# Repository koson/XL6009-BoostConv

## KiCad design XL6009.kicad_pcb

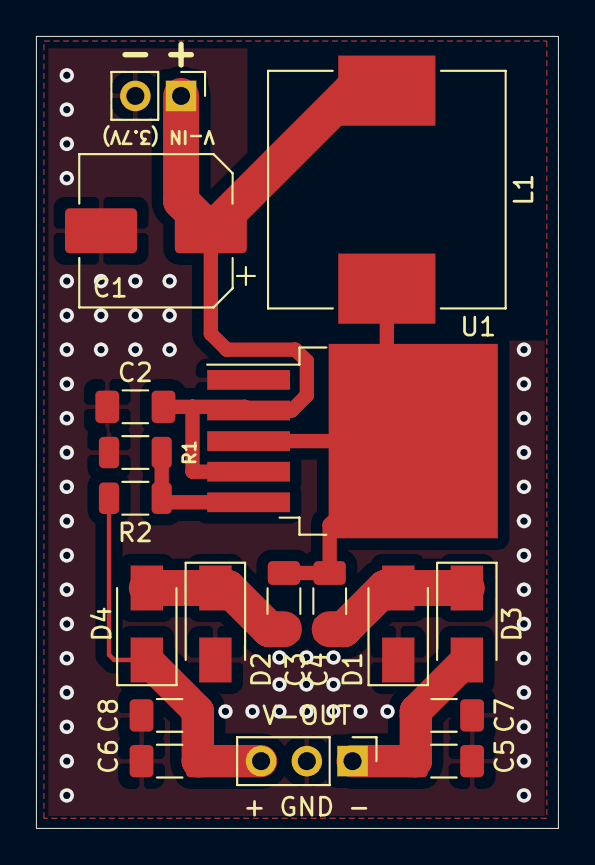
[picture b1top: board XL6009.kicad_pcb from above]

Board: 2 copper layers, 29.0 x 44.0 mm, 18 parts (0 on the bottom side), 8 nets.

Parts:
C1: 330u; CP_Elec_8x6.5
C2, C3, C4, C5, C6, C7, C8: 10u; C_1206_3216Metric_Pad1.33x1.80mm_HandSolder
D1, D2, D3, D4: SS34; D_SMA
J1: Conn_01x02_Female; PinHeader_1x02_P2.54mm_Vertical
J2: Conn_01x03_Female; PinHeader_1x03_P2.54mm_Vertical
L1: 22uH / 2A; L_Neosid_SM-NE127_HandSoldering
R1: RFB2; R_1206_3216Metric
R2: RFB1; R_1206_3216Metric
U1: XL6009; TO-263-5_TabPin3

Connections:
GND: C1.2, C2.1, C5.2, C6.1, C7.2, C8.1, D1.1, D2.2, J1.2, J2.2, R1.2, U1.1
unnamed: C1.1, C2.2, J1.1, L1.1, U1.2, U1.4
unnamed: C3.1, D1.2, D3.1
unnamed: C3.2, C4.2, L1.2, U1.3
unnamed: C4.1, D2.1, D4.2
unnamed: C5.1, C7.1, D3.2, J2.1
unnamed: C6.2, C8.2, D4.1, J2.3, R2.1
unnamed: R1.1, R2.2, U1.5

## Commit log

2021-01-28 initial build
2021-01-28 Screenshoot
2021-01-29 Rev. A
2023-03-28 initial
